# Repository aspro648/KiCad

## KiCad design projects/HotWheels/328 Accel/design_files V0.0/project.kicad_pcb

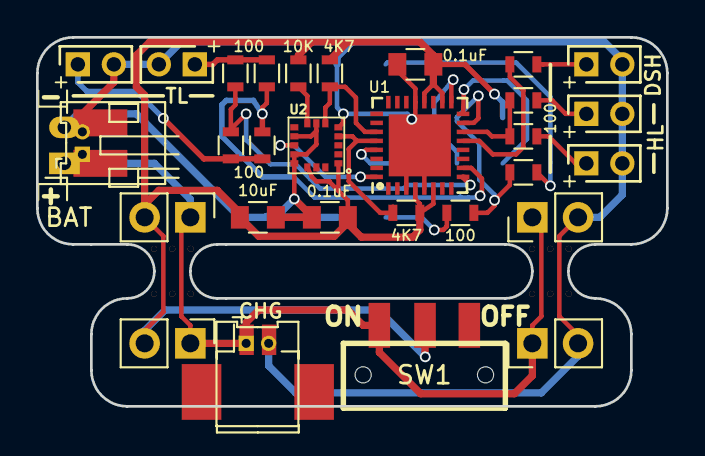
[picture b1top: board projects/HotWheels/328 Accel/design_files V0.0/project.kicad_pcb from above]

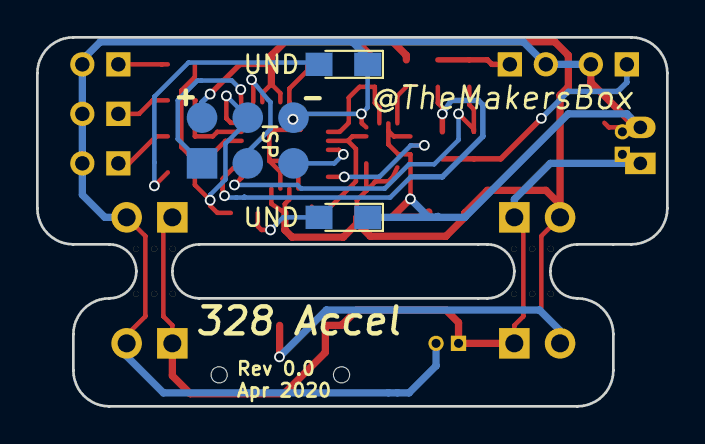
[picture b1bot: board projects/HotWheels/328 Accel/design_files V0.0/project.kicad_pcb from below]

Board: 2 copper layers, 35.0 x 20.5 mm, 34 parts (3 on the bottom side), 22 nets.

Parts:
C1: 10uF; C_0805
C2, C3: 0.1uF; C_0805
CON1: ISP; Pin_Header_Straight_2x03_Pitch2.54mm
D4, D5: UND; LED_0805_HandSoldering
J1, J6: HL; PIN_HEADER_LED
J2: CHG; Molex_PicoBlade_53048-0210_02x1.25mm_Angled
J2#2: Molex_PicoBlade_53261-0271_02x1.25mm_Angled
J3: BAT; Molex_PicoBlade_53048-0210_02x1.25mm_Angled
J4, J5, J44, J55: CONN; Pin_Header_Straight_1x02_Pitch2.54mm
J7, J8: TL; PIN_HEADER_LED
J9: DSH; PIN_HEADER_LED
J10: JST_PH; JST_PH_S2B-PH-K_02x2.00mm_Angled
R1: 10K; R_0603
R2, R3: 4K7; R_0603
R4, R5, R6, R7, R8, R9, R10, R11, R12: 100; R_0603
SW1: SW_SPDT; SPST_SMD
U1: ATMEGA328-MU; QFN-32-1EP_5x5mm_Pitch0.5mm
U2: LIS3DH

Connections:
/D2: U1.32, U2.11
/D5: R4.1, R9.1, U1.9
/D6: R5.1, R8.1, U1.10
/D9: R10.1, U1.13
/D10: R6.1, R7.1, U1.14
/MISO: CON1.1, U1.16
/MOSI: CON1.4, R11.1, R12.1, U1.15
/SCK: CON1.3, U1.17
/SCL: R3.2, U1.28, U2.4
/SDA: R2.2, U1.27, U2.6
/~CS: R1.2, U2.8
/~RESET: CON1.5, U1.29
GND: C1.2, C2.2, C3.2, CON1.6, D4.1, D5.1, J1.2, J2.2, J3.2, J5.2, J6.2, J7.2, J8.2, J9.2, J10.2, J55.2, U1.3, U1.5, U1.21, U2.5, U2.7, U2.10, U2.12, U2.13
unnamed: D4.2, R11.2
unnamed: D5.2, R12.2
unnamed: J1.1, R6.2
unnamed: J6.1, R7.2
unnamed: J7.1, R4.2, R8.2
unnamed: J8.1, R5.2, R9.2
unnamed: J9.1, R10.2
unnamed: J2.1, J3.1, J4.1, J5.1, J10.1, J44.1, J55.1, SW1.1
VCC: C1.1, C2.1, C3.1, CON1.2, J4.2, J44.2, R1.1, R2.1, R3.1, SW1.2, U1.4, U1.6, U1.18, U1.20, U2.1, U2.14

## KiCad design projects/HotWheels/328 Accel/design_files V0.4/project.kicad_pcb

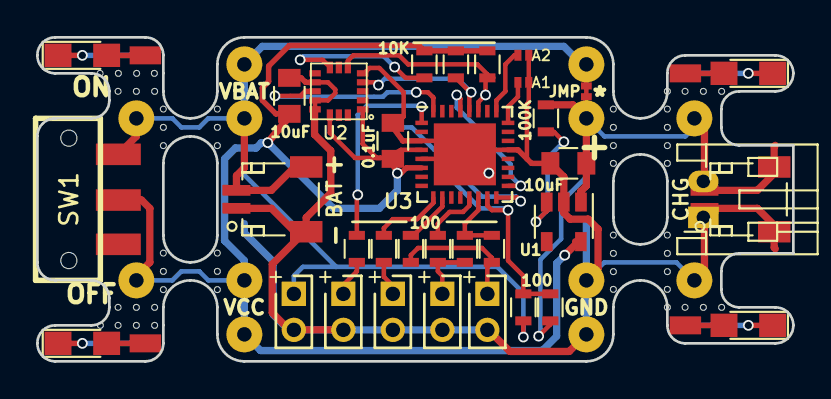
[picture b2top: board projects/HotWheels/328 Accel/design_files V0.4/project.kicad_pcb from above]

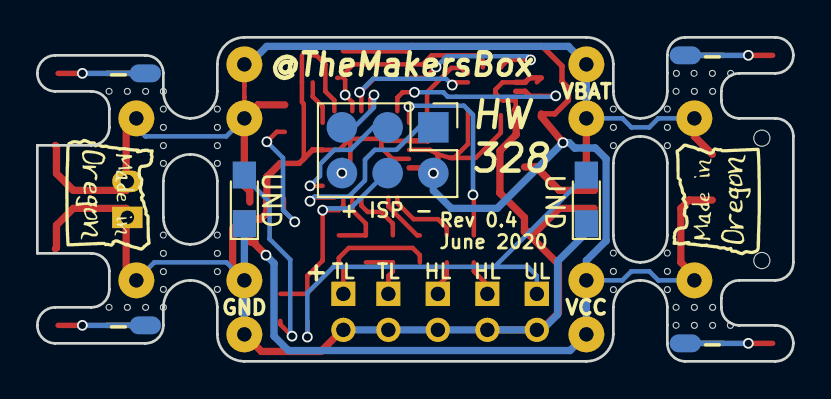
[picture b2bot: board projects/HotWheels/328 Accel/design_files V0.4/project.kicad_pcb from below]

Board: 2 copper layers, 42.0 x 18.0 mm, 55 parts (3 on the bottom side), 33 nets.

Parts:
C1: 0.1uF; C_0805
C2, C3: 10uF; C_0805
CON1: AVR-ISP-6; Pin_Header_Straight_2x03_Pitch2.54mm
D1, D2, D3, D6: LED; LED_0805_HandSoldering
D4, D5: UND; LED_0805_HandSoldering
J1, J6: HL; PIN_HEADER_LED
J2: CHG; JST_SH_SM02B-SRSS-TB_02x1.00mm_Angled
J3: BAT; JST_SH_SM02B-SRSS-TB_02x1.00mm_Angled
J4, J5, J9, J10: LED; LED_PADS
J7, J8: TL; PIN_HEADER_LED
J11: UL; PIN_HEADER_LED
J22: CHG; JST_PH_S2B-PH-K_02x2.00mm_Angled
J44, J45, J46, J47, J48, J49, J54, J55, J56, J57, J58, J59: Conn; SolderWirePad_single_0-8mmDrill
JP1: JMP; Jumper
JP2: A2; Jumper
JP3: A1; Jumper
R1: 100K; R_0603
R2, R3, R4: 10K; R_0603
R5, R6, R7, R8, R9, R10, R11, R12: 100; R_0603
SW1: SW_SPDT; SPST_SMD
U1: MIC5225-3.3; SOT-23-5
U2: LIS3DH; LIS3DH_EP
U3: ATMEGA328-MU; QFN-32-1EP_5x5mm_Pitch0.5mm
VAL: MadeInOregonRev25
VAL#2: MadeInOregonRev25

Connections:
+BATT: C2.1, J2.2, J3.2, J22.2, J44.1, J46.1, J48.1, J54.1, J56.1, J58.1, JP1.1, JP1.2, R1.1, SW1.1, U1.1
/A1: JP3.1, U3.24
/A2: JP2.1, U3.25
/D2: U2.11, U3.32
/D3: R6.1, U3.1
/D5: R7.1, U3.9
/D6: R8.1, U3.10
/D9: R9.1, U3.13
/D10: R5.1, R10.1, U3.14
/MISO: CON1.1, U3.16
/MOSI: CON1.4, R11.1, R12.1, U3.15
/RESET: CON1.5, U3.29
/SCK: CON1.3, U3.17
/SCL: R4.1, U2.4, U3.28
/SDA: R3.1, U2.6, U3.27
GND: C1.2, C2.2, C3.2, CON1.6, D4.1, D5.1, J1.2, J2.1, J3.1, J6.2, J7.2, J8.2, J11.2, J22.1, J45.1, J47.1, J49.1, JP2.2, JP3.2, U1.2, U2.5, U2.10, U2.12, U2.13, U3.3, U3.5, U3.21
unnamed: D1.1, J4.2
unnamed: D1.2, J4.1
unnamed: D2.1, J5.2
unnamed: D2.2, J5.1
unnamed: D3.1, J9.2
unnamed: D3.2, J9.1
unnamed: D4.2, J11.1, R11.2
unnamed: D5.2, R12.2
unnamed: D6.1, J10.2
unnamed: D6.2, J10.1
unnamed: J1.1, R6.2
unnamed: J6.1, R7.2
unnamed: J7.1, R5.2, R8.2
unnamed: J8.1, R9.2, R10.2
unnamed: R1.2, U1.3
unnamed: R2.1, U2.8
VCC: C1.1, C3.1, CON1.2, J55.1, J57.1, J59.1, R2.2, R3.2, R4.2, SW1.2, U1.5, U2.1, U2.14, U3.4, U3.6

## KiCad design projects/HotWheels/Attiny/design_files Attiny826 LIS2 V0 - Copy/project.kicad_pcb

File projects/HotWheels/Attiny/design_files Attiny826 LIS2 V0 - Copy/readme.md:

LIS2 board for LED Lights

Project website: MakersBox.us

Bill Of Materials
----------------
- 1 ea., Perfect Purple PCB from OSH Park, with not so perfect layout from [design_files/project.kicad_pcb](project.kicad_pcb) file.
- 1 ea., LIS2DH12TR, ACCEL 2-16G I2C/SPI 12LGA, https://www.digikey.com/short/2hhnjtq9
- 1 ea., LIS2HH12TR, ACCELEROMETER 2-8G I2C/SPI 12LGA, https://www.digikey.com/short/5dww281d
- 1 ea., IC REG LINEAR 3.3V 200MA SMV SOT-753
    - Toshiba TCR2EF33, https://www.digikey.com/short/twnnv0q2
	- Diodes Incorporated AP7354-33W5-7, https://www.digikey.com/short/mwt0cr4v
- 3 ea., MOSFET N-CH 60V 280MA SOT323-3
    - Nexperia USA Inc., BSS138PW, https://www.digikey.com/short/zbn8bp5t
    - Infineon Technologies, BSS138WH6433XTMA1, https://www.digikey.com/short/9pr0qbn3
	- Diodes Inc BSS138W-7-F, https://www.digikey.com/short/ptn4zw78 
- 1 ea., CAP CER 10uF 50V 0805,
- 3 ea., CAP CER 0.1uF 0605
- 6 ea., 4.7K SMD 0605
- 2 ea., 10K SMD 0605

Revisions
------------------

License
----------------
[Attribution-ShareAlike 3.0 United States (CC BY-SA 3.0 US)](https://creativecommons.org/licenses/by-sa/3.0/us/)

You are free to:

- Share — copy and redistribute the material in any medium or format
- Adapt — remix, transform, and build upon the material

Under the following terms:

- Attribution — You must give appropriate credit, provide a link to the license, and indicate if changes were made. You may do so in any reasonable manner, but not in any way that suggests the licensor endorses you or your use.
- ShareAlike — If you remix, transform, or build upon the material, you must distribute your contributions under the same license as the original.

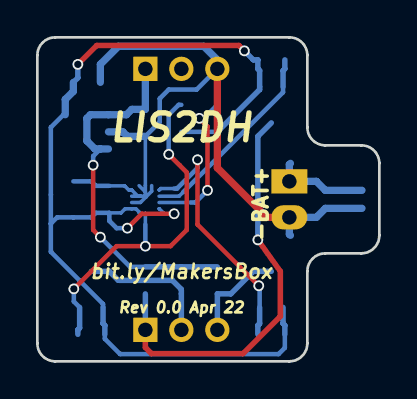
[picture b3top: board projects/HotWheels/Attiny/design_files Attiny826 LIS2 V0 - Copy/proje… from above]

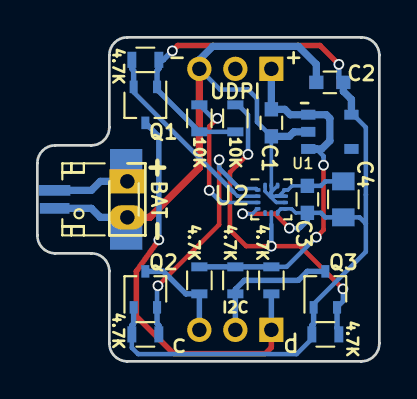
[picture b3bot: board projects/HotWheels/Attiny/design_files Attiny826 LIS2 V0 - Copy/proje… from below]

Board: 2 copper layers, 19.0 x 18.0 mm, 21 parts (21 on the bottom side), 11 nets.

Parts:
C1, C2, C3: 0.1uF; C_0603
C4: 10uF; C_0805
J1: JST-SH; JST_SH_SM02B_hand_solder
J2: BAT; PIN_HEADER_LED
J4: UDPI; PinHeader_1x03_P2.00mm_Vertical
J8: I2C; PinHeader_1x03_P2.00mm_Vertical
Q1, Q2, Q3: BSS138; SOT-323_SC-70
R1, R2, R3, R4, R5, R6: 4.7K; R_0603
R7, R8: 10K; R_0603
U1: Linear 3.3V; SOT-753
U2: LIS2DH; LGA-14_2x2mm_P0.35mm_LayoutBorder3x4y

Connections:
+3V3: C2.1, C3.1, C4.1, Q1.1, Q2.1, Q3.1, R4.1, R5.1, R6.1, R7.1, R8.1, U1.5, U2.4, U2.7, U2.8
/INT: J8.2, Q3.3, R3.2
/INT_3V3: Q3.2, R6.2, R8.2, U2.6
/SCL: J8.3, Q2.3, R2.2
/SCL_3V3: Q2.2, R5.2, U2.1
/SDA: J8.1, Q1.3, R1.2
/SDA_3V3: Q1.2, R4.2, U2.2
GND: C1.2, C2.2, C3.2, C4.2, J1.1, J2.2, J4.3, U1.2, U2.9, U2.10, U2.11, U2.12, U2.13, U2.14
unnamed: J1.2, J2.1
unnamed: R7.2, U2.3
VCC: C1.1, J4.1, R1.1, R2.1, R3.1, U1.1, U1.3
